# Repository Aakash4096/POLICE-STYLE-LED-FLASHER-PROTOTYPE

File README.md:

# POLICE-STYLE-LED-FLASHER-PROTOTYPE
## INTRODUCTION    

•	This project is a police-style LED flasher built using the popular 555 Timer IC. 
•	The circuit uses two 555 timers (IC 555-2) arranged in simple astable mode to generate blinking signals. 
•	It operates from a 9V battery, making it suitable for: 
    o	Model vehicles 
    o	Emergency display units 
o	Electronics hobby demonstrations 
•	The flashing pattern is created by alternating a Red LED and a Blue LED, commonly used in police lights. 
•	The design focuses on: 
o	Minimal components 
o	Stable flashing 
o	Simple timing control using RC networks. 
-----------------------------------------------------------------------------------------------------------

## COMPONENTS USED   

1. 555 TIMER IC (2 Pieces)
2. RESISTORS (47Ω × 2, 1MΩ × 2)
3. CAPACITORS (1µF Polarized + 100nF Ceramic)
4. LEDs (Red + Blue)
5. 12V/9V Battery
6. Buzzer
7. Zero PCB
-----------------------------------------------------------------------------------------------------------
## CIRCUIT CONNECTIONS   

### KiCAD model  

### LtSpice Model

### Final outcome(real-time)  

-----------------------------------------------------------------------------------------------------------

### Working Principle   

1. Charging Phase (Output HIGH) 
•	The 1µF capacitor charges through R1 and 0.1µF capacitor charges through R3  . 
•	While it charges from 1/3 Vcc → 2/3 Vcc, the 555 output (Pin 3) stays HIGH. 
•	This turns Red LED ON (Blue OFF). 
2. Threshold Point Reached 
•	When capacitor voltage hits 2/3 of 12V, 
 → Upper comparator triggers 
 → Flip-flop resets 
 → Output goes LOW 
 → Discharge transistor activates 
3. Discharging Phase (Output LOW) 
•	The capacitor discharges only through R2 . 
•	During discharge from 2/3 Vcc → 1/3 Vcc, 
 → Output stays LOW 
 → Blue LED turns ON (Red OFF). 
4. Trigger Point Reached 
•	When voltage reaches 1/3 Vcc, 
 → Lower comparator triggers 
 → Flip-flop sets 
 → Output returns HIGH 
The cycle repeats endlessly. 
-----------------------------------------------------------------------------------------------------------

### Timing Formula for 555 Astable Mode   

#### First 555IC   

•	ONE timing resistor (1ΜΩ) 
•	ONE timing capacitor (1µF) 
•	A diode around the capacitor making charge/discharge symmetrical 
•	The ON and OFF times use the same formula: 
T=0.693 ×R×C 
So: 
Charging time (output HIGH): 
•	THIGH = 0.693 × 1ΜΩ × 1μF THIGH = 0.693 seconds 
Discharging time (output LOW): 
Same resistor, same capacitor. 
•	TLOW = 0.693 × 1ΜΩ × 1μF 
•	TLOW = 0.693 seconds 
3. TOTAL Flash Period 
TTOTAL THIGH + TLOW T=0.693+0.6931.386 seconds 
Full flash cycle ≈ 1.4 seconds 
About 0.7 seconds ON and 0.7 seconds OFF 
#### Second 555IC   

Full flash cycle ≈ 1.4 seconds/10=0.14s 

-----------------------------------------------------------------------------------------------------------

### What We Learned From This Project   

1. Understanding of Electronic Components 
2. KiCad PCB Design Knowledge 
3. LTSpice Simulation Skills 
4. Real-Time Testing and Troubleshooting 
5. Hands-on Experience 

-----------------------------------------------------------------------------------------------------------

### Conclusion   

Built a fully functional Police Light + Siren Unit. 
Combined visual signaling (LED flashes) with audio signaling (buzzer). 
Successfully implemented: 
•	Design → Simulation → PCB → Soldering → Testing → Final working model 
Gained both theoretical knowledge and hands-on engineering experience. 

#### PDF/DOCX link
https://github.com/Aakash4096/POLICE-STYLE-LED-FLASHER-PROTOTYPE/blob/main/Project_Assets/POLICE-STYLE%20LED%20FLASHER.pdf
https://github.com/Aakash4096/POLICE-STYLE-LED-FLASHER-PROTOTYPE/blob/main/Project_Assets/POLICE-STYLE%20LED%20FLASHER.docx
-----------------------------------------------------------------------------------------------------------

## THANKING OUR TEAM
#### Project Performed By :  
1. KUSHAL GARG ( 2024UEC1635 ) 
2. VIRENDER MEENA ( 2024UEC1711) 
3. RAHUL LAMBA ( 2024UEC1704 ) 
4. PRIYANSHU MEEL ( 2024UEC1714 ) 
5. AAKASH KUMAR( 2024UEC1706 ) 

#### Under Guidance Of : 
•Dr. Ritu Sharma 
•Sonu Jain

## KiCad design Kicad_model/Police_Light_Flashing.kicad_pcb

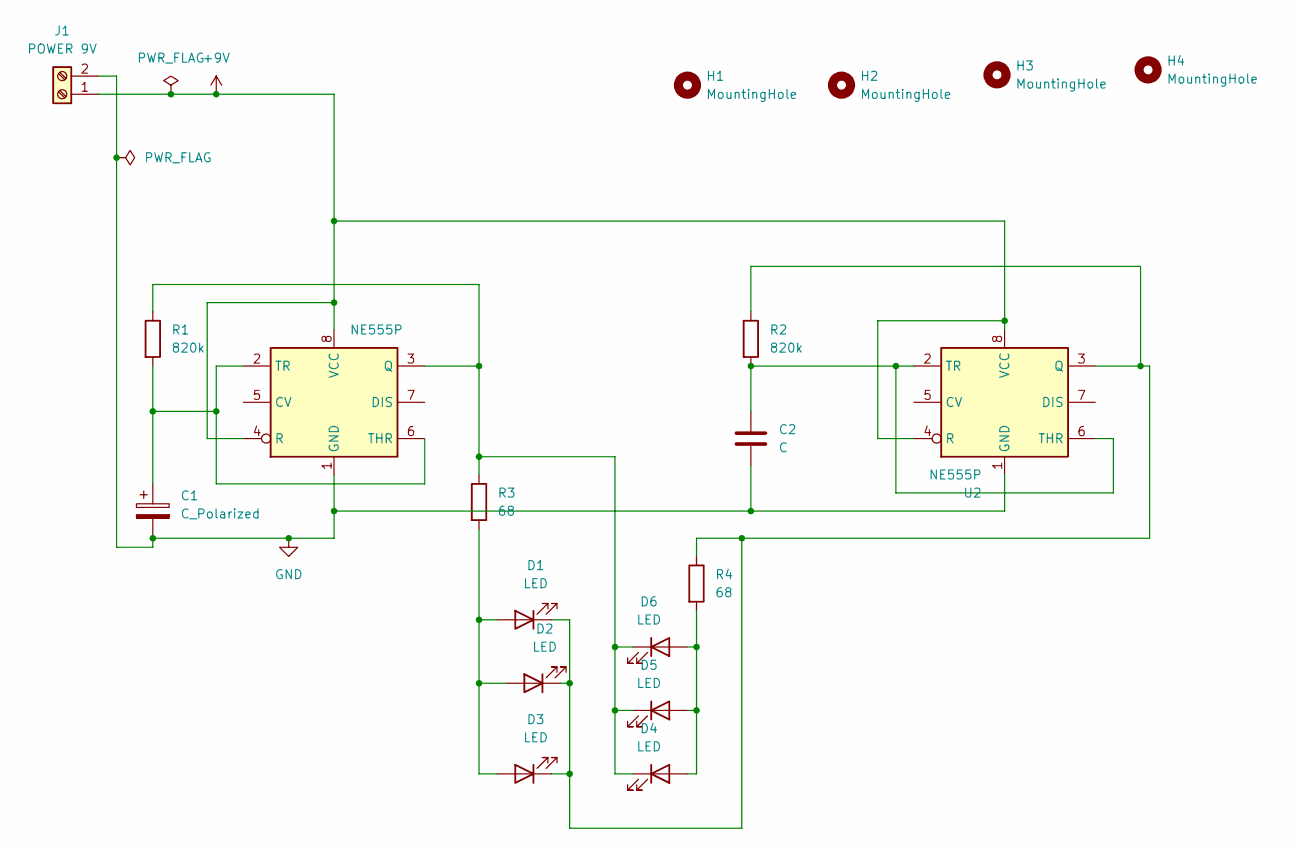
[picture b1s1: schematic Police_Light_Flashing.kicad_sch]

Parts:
C1: C_Polarized; CP_Radial_D4.0mm_P2.00mm
C2: C; C_Disc_D3.4mm_W2.1mm_P2.50mm
D1, D2, D3, D4, D5, D6: LED; LED_D5.0mm
H1, H2, H3, H4: MountingHole; MountingHole_2.5mm_Pad
J1: POWER 9V; TerminalBlock_MaiXu_MX126-5.0-02P_1x02_P5.00mm
R1, R2: 820k; R_Axial_DIN0204_L3.6mm_D1.6mm_P7.62mm_Horizontal
R3, R4: 68; R_Axial_DIN0204_L3.6mm_D1.6mm_P7.62mm_Horizontal
U1, U2: NE555P; DIP-8_W7.62mm

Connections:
+9V: J1.1, U1.4 (R), U1.8 (VCC), U2.4 (R), U2.8 (VCC)
GND: C1.2, C2.2, J1.2, U1.1 (GND), U2.1 (GND)
unnamed: D1.2 (A), D2.2 (A), D3.2 (A), R3.2
unnamed: D1.1 (K), D2.1 (K), D3.1 (K), R2.1, R4.1, U2.3 (Q)
unnamed: D4.2 (A), D5.2 (A), D6.2 (A), R4.2
unnamed: D4.1 (K), D5.1 (K), D6.1 (K), R1.1, R3.1, U1.3 (Q)
unnamed: C1.1, R1.2, U1.2 (TR), U1.6 (THR)
unnamed: C2.1, R2.2, U2.2 (TR), U2.6 (THR)

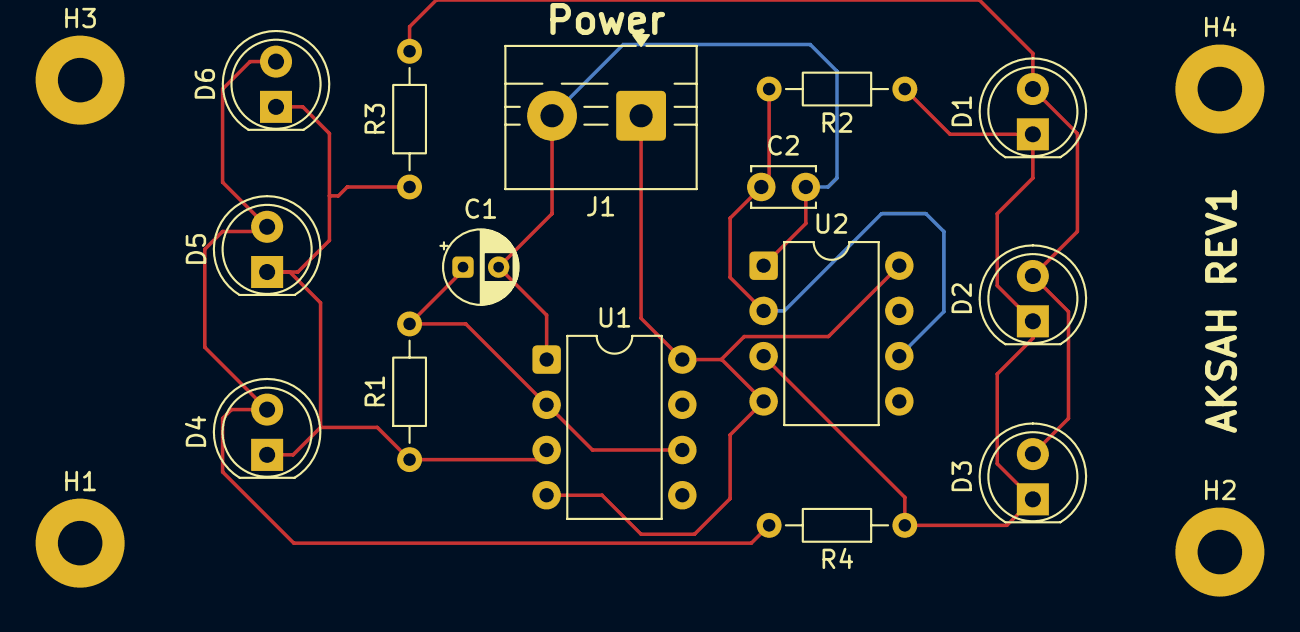
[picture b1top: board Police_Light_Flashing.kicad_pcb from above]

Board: 2 copper layers, 19 parts (0 on the bottom side), 8 nets.

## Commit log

2025-12-06 Revised schematic with KiCAD
2025-12-06 Revised schematic with KiCAD ,ltspice and docx/pdf
2025-12-06 Enhance README with project details and components
    Expanded the README with project introduction, components used, and circuit connections.
2025-12-06 Fix formatting and update section titles in README
2025-12-06 Number team members for clarity in README
2025-12-09 Refactor README formatting and add images
    Updated formatting and added images for clarity.
2025-12-09 Add GitHub Actions workflow for Jekyll deployment
    This workflow automates the building and deployment of a Jekyll site to GitHub Pages, including steps for checking out the code, building the site, and deploying it.
2025-12-09 Improve formatting in README.md
    Added additional spacing and formatting for clarity.
2025-12-09 Fix image links in README.md
    Updated image links in the README for clarity.
2025-12-09 Fix image links in README.md
    Updated image links in README to use 'blob' instead of 'tree' for proper rendering.
2025-12-09 Update README with PDF and DOCX links
    Added links to PDF and DOCX files in the README.
